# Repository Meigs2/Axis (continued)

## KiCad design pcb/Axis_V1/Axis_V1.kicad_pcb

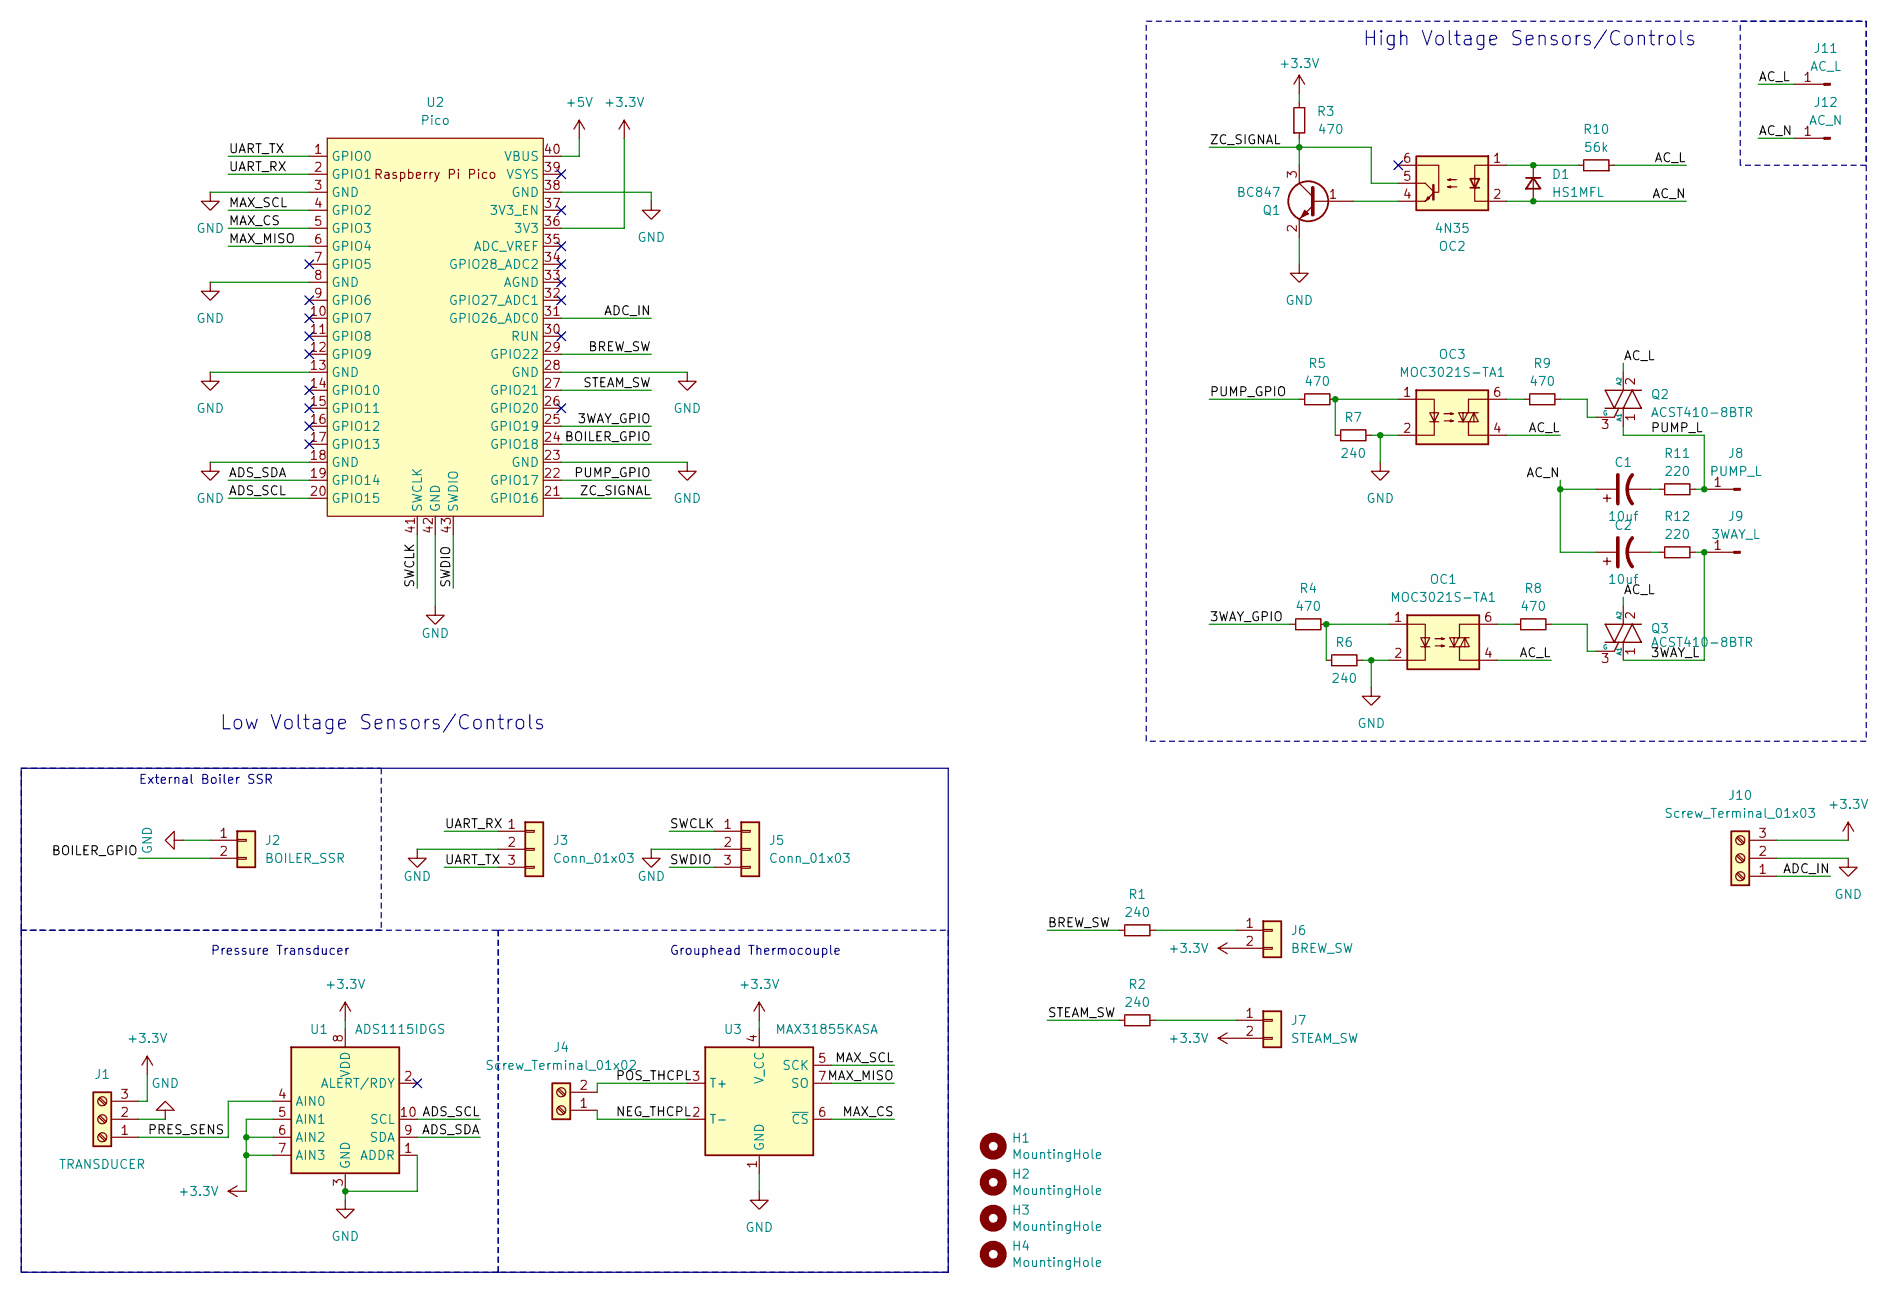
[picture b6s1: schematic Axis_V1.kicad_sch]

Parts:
C1, C2: 10uf; C_1206_3216Metric
D1: HS1MFL; D_SOD-123
H1, H2, H3, H4: MountingHole; MountingHole_4.3mm_M4
J1: TRANSDUCER; TerminalBlock_MetzConnect_Type073_RT02603HBLU_1x03_P5.08mm_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
J2: BOILER_SSR; JST_PH_B2B-PH-K_1x02_P2.00mm_Vertical
J3, J5: Conn_01x03; 1x03 Pin Header Holes
J4: Screw_Terminal_01x02; TerminalBlock_MetzConnect_Type101_RT01602HBWC_1x02_P5.08mm_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
J6: BREW_SW; JST_PH_B2B-PH-K_1x02_P2.00mm_Vertical
J7: STEAM_SW; JST_PH_B2B-PH-K_1x02_P2.00mm_Vertical
J8: PUMP_L; Quick Disconnect
J9: 3WAY_L; Quick Disconnect
J10: Screw_Terminal_01x03; JST_PH_B3B-PH-K_1x03_P2.00mm_Vertical
J11: AC_L; Quick Disconnect
J12: AC_N; Quick Disconnect
OC1, OC3: MOC3021S-TA1; SMDIP-6_W7.62mm
OC2: 4N35; SMDIP-6_W7.62mm
Q1: BC847; SOT-23
Q2, Q3: ACST410-8BTR; TO-252-2
R1, R2, R6, R7: 240; R_1206_3216Metric
R3, R4, R5: 470; R_1206_3216Metric
R8, R9: 470; R_2512_6332Metric
R10: 56k; R_2512_6332Metric
R11, R12: 220; R_2512_6332Metric
U1: ADS1115IDGS; TSSOP-10_3x3mm_P0.5mm
U2: Pico; RPi_Pico_SMD_TH
U3: MAX31855KASA; SOIC-8_3.9x4.9mm_P1.27mm

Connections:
+3.3V: J1.3, J6.2, J7.2, J10.3, R3.2, U1.5 (AIN1), U1.6 (AIN2), U1.7 (AIN3), U1.8 (VDD), U2.36 (3V3), U3.4 (V_CC)
+5V: U2.40 (VBUS)
/3WAY_GPIO: R4.1, U2.25 (GPIO19)
/3WAY_L: J9.1, Q3.1 (A1), R12.2
/AC_L: J11.1, OC1.4, OC3.4, Q2.2 (A2), Q3.2 (A2), R10.1
/AC_N: C1.1, C2.1, D1.2 (A), J12.1, OC2.2
/ADC_IN: J10.1, U2.31 (GPIO26_ADC0)
/ADS_SCL: U1.10 (SCL), U2.20 (GPIO15)
/ADS_SDA: U1.9 (SDA), U2.19 (GPIO14)
/BOILER_GPIO: J2.2, U2.24 (GPIO18)
/BREW_SW: R1.1, U2.29 (GPIO22)
/MAX_CS: U2.5 (GPIO3), U3.6 (~CS)
/MAX_MISO: U2.6 (GPIO4), U3.7 (SO)
/MAX_SCL: U2.4 (GPIO2), U3.5 (SCK)
/NEG_THCPL: J4.1, U3.2 (T-)
/POS_THCPL: J4.2, U3.3 (T+)
/PRES_SENS: J1.1, U1.4 (AIN0)
/PUMP_GPIO: R5.1, U2.22 (GPIO17)
/PUMP_L: J8.1, Q2.1 (A1), R11.2
/STEAM_SW: R2.1, U2.27 (GPIO21)
/SWCLK: J5.1, U2.41 (SWCLK)
/SWDIO: J5.3, U2.43 (SWDIO)
/UART_RX: J3.1, U2.2 (GPIO1)
/UART_TX: J3.3, U2.1 (GPIO0)
/ZC_SIGNAL: OC2.5, Q1.3 (C), R3.1, U2.21 (GPIO16)
GND: J1.2, J2.1, J3.2, J5.2, J10.2, OC1.2, OC3.2, Q1.2 (E), R6.2, R7.2, U1.1 (ADDR), U1.3 (GND), U2.3 (GND), U2.8 (GND), U2.13 (GND), U2.18 (GND), U2.23 (GND), U2.28 (GND), U2.38 (GND), U2.42 (GND), U3.1 (GND)
unnamed: C1.2, R11.1
unnamed: C2.2, R12.1
unnamed: D1.1 (K), OC2.1, R10.2
unnamed: J6.1, R1.2
unnamed: J7.1, R2.2
unnamed: OC1.1, R4.2, R6.1
unnamed: OC1.6, R8.1
unnamed: OC3.1, R5.2, R7.1
unnamed: OC3.6, R9.1
unnamed: OC2.4, Q1.1 (B)
unnamed: Q2.3 (G), R9.2
unnamed: Q3.3 (G), R8.2

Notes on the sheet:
High Voltage Sensors/Controls
Grouphead Thermocouple
External Boiler SSR
Low Voltage Sensors/Controls
Pressure Transducer

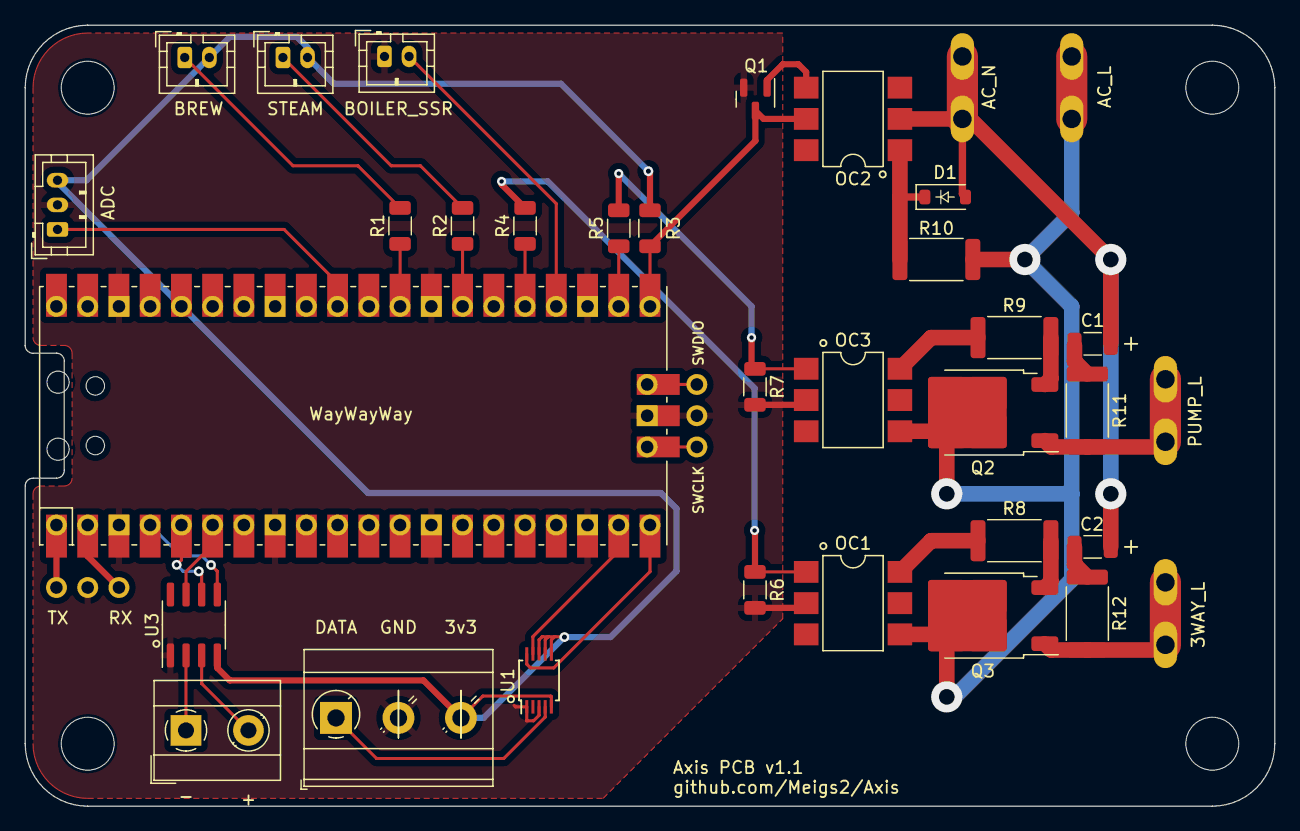
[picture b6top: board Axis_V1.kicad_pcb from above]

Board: 2 copper layers, 101.6 x 63.5 mm, 40 parts (0 on the bottom side), 37 nets.

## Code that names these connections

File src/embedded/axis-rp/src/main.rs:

#![no_std]
#![no_main]
#![feature(type_alias_impl_trait)]
#![feature(async_closure)]
#![feature(never_type)]

mod client_communicator;
mod systems;
mod runtime;
mod drivers;

use core::cmp::max;
use {defmt_rtt as _, panic_probe as _};
use core::future::Future;
use core::ops::Deref;
use assign_resources::assign_resources;
use cortex_m::prelude::_embedded_hal_blocking_i2c_Write;
use defmt::{error, info, unwrap};
use defmt::Format;
use embassy_embedded_hal::shared_bus::asynch::i2c::I2cDevice;
use embassy_embedded_hal::shared_bus::asynch::spi::SpiDevice;
use embassy_executor::{Executor, InterruptExecutor, Spawner};
use embassy_rp::interrupt::{InterruptExt, Priority};
use embassy_rp::multicore::{spawn_core1, Stack};
use embassy_rp::{bind_interrupts, i2c, spi, interrupt};
use embassy_rp::gpio::{AnyPin, Level, Output};
use embassy_rp::i2c::{Config, Error, I2c};
use embassy_time::{Duration, Instant, Timer};
use serde::{Deserialize, Serialize};
use serde_json_core::heapless::String;
use static_cell::{make_static, StaticCell};
use Message::*;
use embassy_rp::peripherals;
use embassy_rp::peripherals::{I2C0, I2C1, SPI0, SPI1};
use embassy_rp::spi::Spi;
use embassy_sync::blocking_mutex::raw::CriticalSectionRawMutex;
use embassy_sync::mutex::Mutex;
use crate::drivers::ads1119;
use crate::drivers::pca9544a::Channel;

pub const MAX_STRING_SIZE: usize = 64;
pub const MAX_PACKET_SIZE: usize = 64;
pub const THERMOCOUPLE_SPI_FREQUENCY: u32 = 500_000;

pub type SpiBus<'a, T: spi::Instance> = Mutex<CriticalSectionRawMutex, Spi<'a, T, spi::Async>>;
pub type I2cBus<'a, T: i2c::Instance> = Mutex<CriticalSectionRawMutex, I2c<'a, T, i2c::Async>>;

bind_interrupts!(pub struct I2c0Irqs {
    I2C0_IRQ => embassy_rp::i2c::InterruptHandler<I2C0>;
});

bind_interrupts!(pub struct I2c1Irqs {
    I2C1_IRQ => embassy_rp::i2c::InterruptHandler<I2C1>;
});

#[derive(Format, Debug, Serialize, Deserialize)]
pub enum Message {
    Ping,
    Pong { value: String<MAX_STRING_SIZE> },
    ThermocoupleReading { value: f32 },
    AdsReading { value: f32 },
    BrewSwitch { is_on: bool },
}

#[derive(Copy, Clone, Serialize, Deserialize)]
pub enum MessageType {}

#[derive(Debug)]
pub enum MessageError {
    InvalidMessageType,
    Unknown,
}

static EXECUTOR_HIGH: InterruptExecutor = InterruptExecutor::new();
static EXECUTOR_MED: InterruptExecutor = InterruptExecutor::new();
static EXECUTOR_LOW: StaticCell<Executor> = StaticCell::new();

static mut CORE1_STACK: Stack<8192> = Stack::new();
static EXECUTOR_CORE1: StaticCell<Executor> = StaticCell::new();

#[interrupt]
unsafe fn SWI_IRQ_1() {
    EXECUTOR_HIGH.on_interrupt()
}

#[interrupt]
unsafe fn SWI_IRQ_0() {
    EXECUTOR_MED.on_interrupt()
}

pub async fn wait_with_timeout<F: Future>(
    millis: u64,
    fut: F,
) -> Result<F::Output, embassy_time::TimeoutError> {
    embassy_time::with_timeout(Duration::from_millis(millis), fut).await
}

type I2c0Bus = Mutex<CriticalSectionRawMutex, I2c<'static, I2C0, i2c::Async>>;
type I2c1Bus = Mutex<CriticalSectionRawMutex, I2c<'static, I2C1, i2c::Async>>;

type Spi0Bus = Mutex<CriticalSectionRawMutex, Spi<'static, SPI0, spi::Async>>;
type Spi1Bus = Mutex<CriticalSectionRawMutex, Spi<'static, SPI1, spi::Async>>;


assign_resources! {
    i2c0: I2c0Resources {
        peripheral: I2C0,
        sda: PIN_12,
        scl: PIN_13,
    }
    i2c1: I2c1Resources {
        peripheral: I2C1,
        sda: PIN_26,
        scl: PIN_27,
    }
    gpio: ExtraGpios {
        gpio1: PIN_2,
        gpio2: PIN_3,
        gpio3: PIN_4,
        gpio4: PIN_5,
        gpio5: PIN_6,
        gpio6: PIN_7,
    }
    spi0: Spi0Resources {
        spi0_rx:  PIN_16,
        spi0_cs0: PIN_17,
        spi0_sck: PIN_18,
        spi0:     SPI0,
        rx_dma0:   DMA_CH0,
        rx_dma1:   DMA_CH1,
    }
    spi1: Spi1Resources {
        spi1_rx:  PIN_8,
        spi1_cs0: PIN_9,
        spi1_sck: PIN_10,
        spi1_tx:  PIN_11,
        spi1:     SPI1,
        rx_dma0:   DMA_CH2,
    }
    hv_breakout: HighVoltageBreakoutResources {
        hv_io1: PIN_20,
        zc_sig: PIN_21,
        hv_io2: PIN_28
    }
    other: OtherResources {
        led: PIN_25,
    }
}

#[cortex_m_rt::entry]
fn main() -> ! {
    let p = embassy_rp::init(Default::default());
    let r = split_resources!(p);

    let i2c0 = I2c::new_async(r.i2c0.peripheral, r.i2c0.scl, r.i2c0.sda, I2c0Irqs, Config::default());
    let i2c1 = I2c::new_async(r.i2c1.peripheral, r.i2c1.scl, r.i2c1.sda, I2c1Irqs, Config::default());

    let spi0_cs0 = Output::new(r.spi0.spi0_cs0, Level::High);
    let mut spi0_config = spi::Config::default();
    spi0_config.frequency = 1_000_000;

    let spi0 = Spi::new_rxonly(r.spi0.spi0, r.spi0.spi0_sck, r.spi0.spi0_rx, r.spi0.rx_dma0, r.spi0.rx_dma1, spi0_config);

    static I2C0_BUS: StaticCell<I2c0Bus> = StaticCell::new();
    static I2C1_BUS: StaticCell<I2c1Bus> = StaticCell::new();

    static SPI0_BUS: StaticCell<Spi0Bus> = StaticCell::new();
    static SPI1_BUS: StaticCell<Spi1Bus> = StaticCell::new();

    let i2c0_bus = I2C0_BUS.init(I2c0Bus::new(i2c0));
    let i2c1_bus = I2C1_BUS.init(I2c1Bus::new(i2c1));

    let spi0_bus = SPI0_BUS.init(Spi0Bus::new(spi0));

    // High-priority executor: SWI_IRQ_1, priority level 2
    interrupt::SWI_IRQ_1.set_priority(Priority::P2);
    let spawner = EXECUTOR_HIGH.start(interrupt::SWI_IRQ_1);
    unwrap!(spawner.spawn(temp(spi0_cs0, spi0_bus)));

    // Medium-priority executor: SWI_IRQ_0, priority level 3
    interrupt::SWI_IRQ_0.set_priority(Priority::P3);
    let spawner = EXECUTOR_MED.start(interrupt::SWI_IRQ_0);
    unwrap!(spawner.spawn(read_ads(i2c1_bus)));

    // Low priority executor: runs in thread mode, using WFE/SEV
    let executor = EXECUTOR_LOW.init(Executor::new());
    executor.run(|spawner| {
        unwrap!(spawner.spawn(blink(r.other)));
    });
}

#[embassy_executor::task]
async fn temp(cs: Output<'static>, spi_bus: &'static Spi0Bus) {
    let device = SpiDevice::new(spi_bus, cs);

    let mut max = drivers::max31855::Max31855::new(device);

    loop {
        let res = max.read_raw().await;
        match res {
            Ok(value) => {
                info!("Success");
                info!("Temp: {:?}", value.get_temp());
            },
            Err(e) => {
                error!("Error or something :(")
            }
        }
        Timer::after_millis(250).await;
    }
}

#[embassy_executor::task]
async fn blink(other: OtherResources) {
    let mut led = Output::new(other.led, Level::Low);

    loop {
        //info!("led on");
        led.set_high();
        Timer::after_secs(1).await;

        //info!("led off");
        led.set_low();
        Timer::after_secs(1).await;
    }
}

#[embassy_executor::task]
async fn read_ads(bus: &'static I2c1Bus) {
    let mut pca_i2c_device = I2cDevice::new(bus);
    let pca9544a = drivers::pca9544a::Pca9544a::new(&mut pca_i2c_device, 0b111_0000);

    let ads_i2c_device = pca9544a.create_device(Channel::Channel1);
    let mut ads1119 = ads1119::Ads1119::new(ads_i2c_device, 0b100_0000);

    let mut is_setup: bool = false;

    loop {
        Timer::after_secs(1).await;
        if !is_setup {
            let mut config = ads1119::ConfigRegister(0);
            config.set_mux(ads1119::MuxConfig::AIN0_AGND);
            config.set_vref(ads1119::VoltageReference::External);
            config.set_conversion_mode(ads1119::ConversionMode::Continuous);
            ads1119.configure(config).await.unwrap();
            ads1119.start_conversion().await.unwrap();
            is_setup = true;
        }

        Timer::after_millis(500).await;

        let value = ads1119.read_data().await.unwrap();

        info!("Ads Data: {:?}", value);
    }
}

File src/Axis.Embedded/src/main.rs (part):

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
    let runtime = make_static!(Runtime::new(external_channel.sender()));

    let max_scl = p.PIN_18;
    let max_cs = Output::new(p.PIN_21, Level::High);
    let max_miso = p.PIN_20;

    let max_rx_dma = p.DMA_CH3;

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
    let thermocouple = make_static!(MAX31855::new(th_spi, max_cs));

    let ads_sda = p.PIN_14;
    let ads_scl = p.PIN_15;

    let ads_config = AdsConfig {
        sensor_min_voltage: 0.5,
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
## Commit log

2023-07-01 Remove MudBlazor
2023-07-03 Lots-O-Additions
2023-07-04 Setup Dev Environment in VSCode
2023-07-04 Updates, fried the last temerature board lmao
2023-07-06 setup embedded project
2023-07-06 Change SPI frequency
2023-07-07 More rust stuff.
2023-07-08 Getting a slight headache...
2023-07-09 Holy god it builds
2023-07-09 Holy god it builds again
2023-07-09 Updates, realizing I cant use either device as a spi slave. Will prob go over usb at this point.
2023-07-10 WHAT IS HAPPENING
2023-07-10 ok it compiles
2023-07-10 ok it compiles again
2023-07-11 Stuff from last night
2023-07-12 Yapp
2023-07-12 quick changes
2023-07-13 More stuff
2023-07-13 More, MORE
2023-07-13 More too
2023-07-15 I have... no clue. Please help.
2023-07-15 Fixed
2023-07-16 Kinda working, going to manually implement serialization because I'm getting... weirdness.
2023-07-16 Finally working!
2023-07-16 Changes before task refactors
2023-07-16 Refactor into tasks, start using cargo embed.
2023-07-17 We're. Cooking.
2023-07-19 add ads1115.rs
2023-07-19 Updates again
2023-07-19 Stuff again
2023-07-19 More
2023-07-19 Yepp
2023-07-21 Pressure sensor working, roll back max changes
2023-07-23 Lots of changes, mainly checkpoint
2023-07-23 Update nav menu to add navivation to /data
2023-07-24 Get chart loaded properly
2023-07-25 Checkpoint
2023-07-25 Scaling is kinda working. I guess.
2023-07-25 Update graphing code.
2023-07-26 Add start of refactored charting stuff.
2023-07-29 Switch to using chart.js from d3, added ads observable.
2023-07-29 Fix grid not resizing properly.
2023-07-29 Move project from WASM to server-side Blazor (can't interact with GPIO in WASM), add charting for Temperature and Pressure readouts.
2023-07-30 Updates, unfinished.
2023-07-30 Adding a bunch of stuff, going to separate out peripherals, sensors and controllers to hopefully organize the code and make things maintainable.
2023-08-01 Again a bunch of stuff
2023-08-02 Again a bunch of stuff. Dear god getting rust to compile is no_std is a pain
2023-08-03 Got the client communicator in a single struct. Needed? No. Does it work? No clue, we'll see I guess
2023-08-03 Run cargo fmt
2023-08-05 Honestly don't even know anymore, getting some of this to build is actually wild. Can't do async cause I can't use embassy_executor::main. Oh well.
2023-08-05 ... something broken on core 1, great
2023-08-06 yeah so uh, stuff stopped working and I'm having to fix stuff in embassy-rs so we're going back to "just get it to work"
2023-08-06 Thanks pennae and xoviat
2023-08-06 Cleanup, pin version to custom version of embassy with fix for sending USB between threads.
2023-08-06 Well. Fixed a bunch of stuff. Turns out you really gotta make all that stuff static. idk.
2023-08-06 We're working, for some reason you can't run the usb device on core1, you have to run it on core0.
2023-08-07 Got dimming to work last night.
2023-08-07 Add some debugging to the pump dimmer and fix the dimmer staying on constantly.
2023-08-07 Cargo fix + fmt
2023-10-28 Add axis pcb files
2023-10-28 Updates, add Pico MCU from github
2023-10-29 Add more stuff for pcb
2023-10-29 PCB Updates
2023-11-04 More pcb updates
2023-11-04 We're basically there, going to get BOM together.
2023-11-11 V1 updates
2023-11-27 More updates I guess
2023-12-26 More and more pcb updates
2023-12-26 More changes
2023-12-27 v1.1 ordered, updates
2023-12-27 Almost messed it up.
    Moved things around and make sure the rust code and schematics match up.
2024-02-10 schematic updates
2024-03-04 Moreeeeeeeeeeeeee
2024-09-01 Updates to V2 pcb, add HV pcb
2024-09-05 More changes, wow! Who would have thought?
2024-09-05 Add README.md
2024-09-07 More updates and changes
2024-09-07 Added a I2C expander for non-essential peripherals, etc.
2024-09-08 Almost done with v2, getting design review
2024-09-08 Remove old PCB files
2024-09-08 Remove stray .dru file?
2024-09-28 Add "V3"
2024-09-28 Updates to the HV pcb
2024-09-28 Oops haha changes
2024-09-29 Is anyone listening anymore?
2024-09-29 Yuuuuuuuuuuuuuuuuuup, nobody's here
2024-10-05 Ok I'm about to order the HV pcb and parts somebody stop me
2024-10-12 Move stuff around
2024-10-21 Rev 3 Update or something
2024-10-21 updates to embedded project
2024-10-28 updates to embedded project pt 2 updates to embedded project
2024-10-31 Add desktop project, tidy up pca9544a impl
2024-10-31 Remove not required comments, thanks @dirbaio!
2024-11-02 remove .NET project, rename and move axis-rp to axis-embedded
2024-11-02 add shadcn-svelte, add and update svelte-echarts
2024-11-05 small changes
2024-11-05 small additions
2024-12-21 Add V4 pcb
2024-12-24 Add base board
